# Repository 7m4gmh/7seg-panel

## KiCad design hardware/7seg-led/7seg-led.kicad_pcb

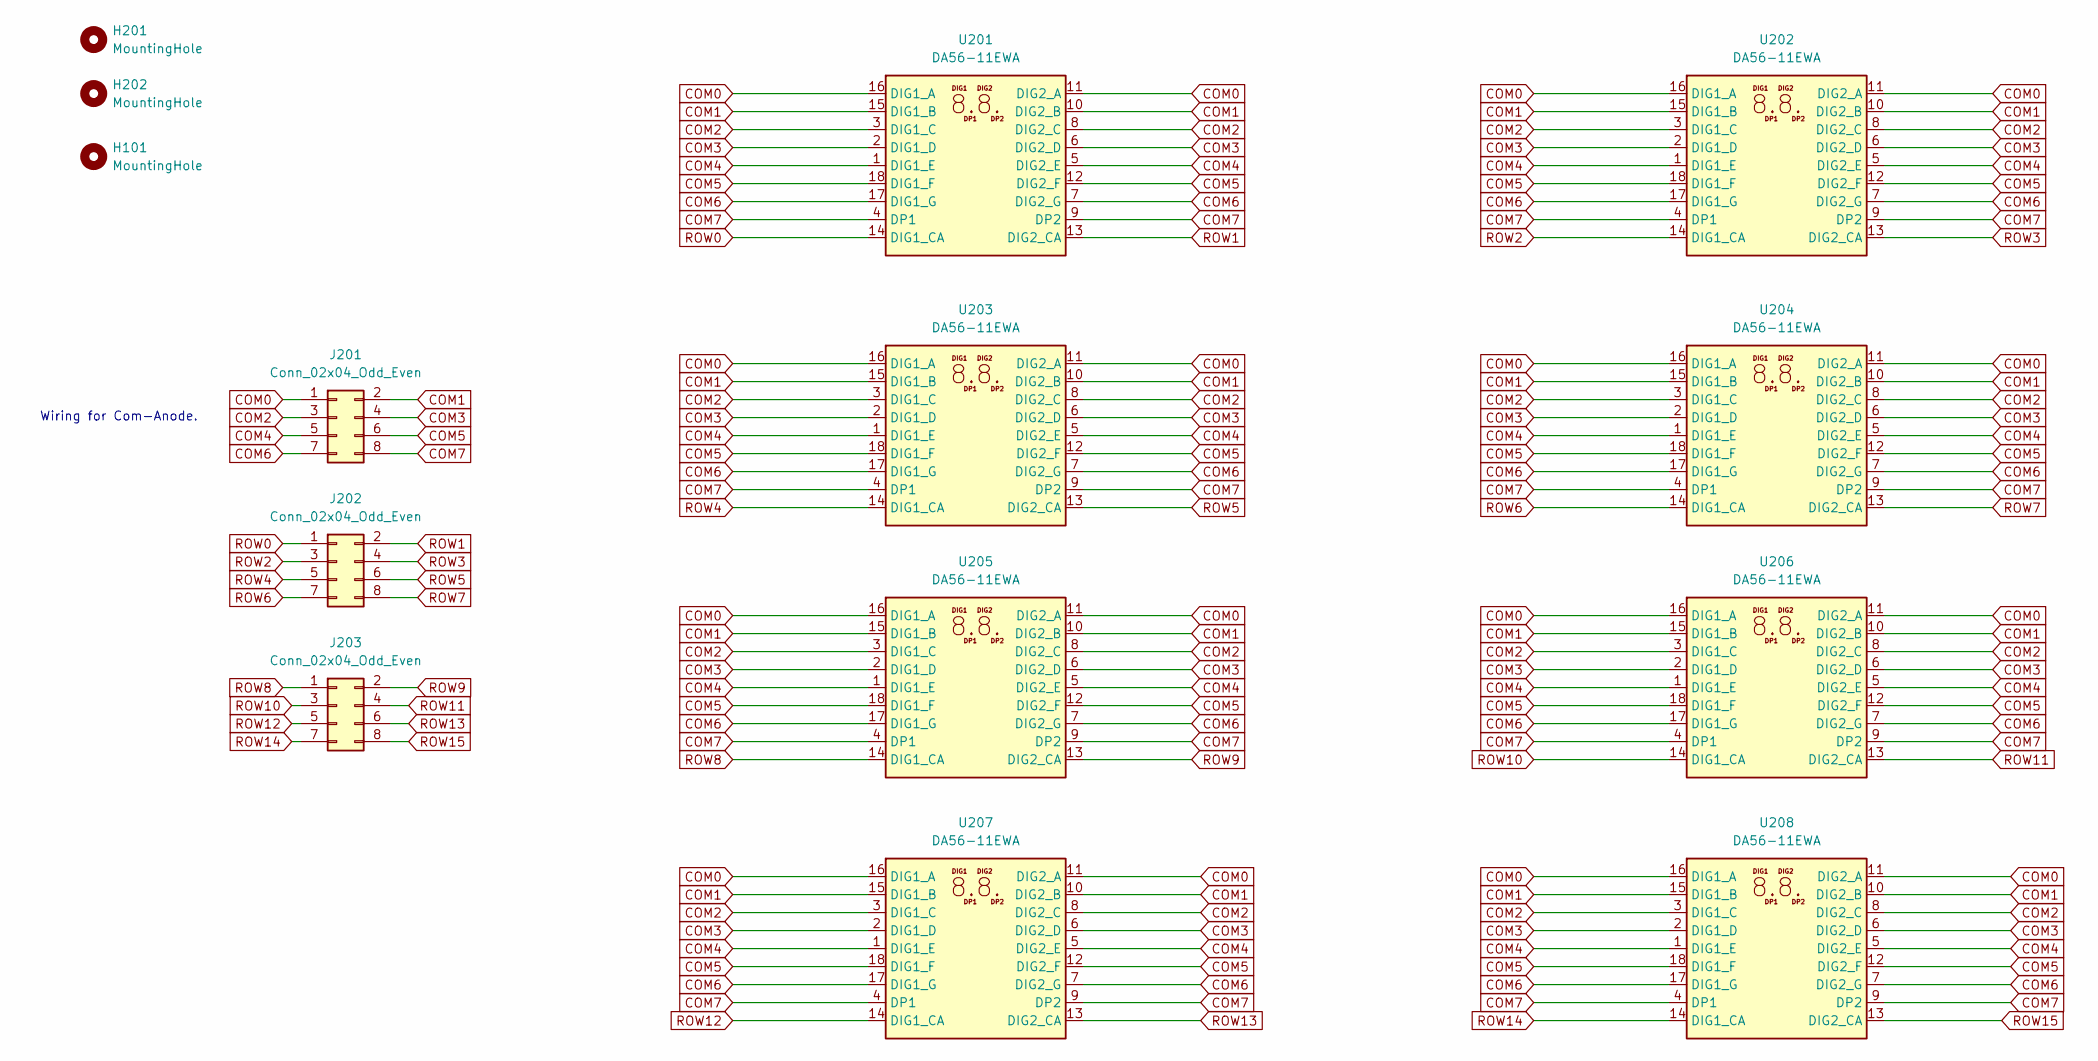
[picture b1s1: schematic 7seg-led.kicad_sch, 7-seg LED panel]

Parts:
H101, H201, H202: MountingHole; MountingHole_3.2mm_M3
J201, J202, J203: Conn_02x04_Odd_Even; PinHeader_2x04_P2.54mm_Vertical
U201, U202, U203, U204, U205, U206, U207, U208: DA56-11EWA; SL-9263

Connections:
COM0: J201.1, U201.11 (DIG2_A), U201.16 (DIG1_A), U202.11 (DIG2_A), U202.16 (DIG1_A), U203.11 (DIG2_A), U203.16 (DIG1_A), U204.11 (DIG2_A), U204.16 (DIG1_A), U205.11 (DIG2_A), U205.16 (DIG1_A), U206.11 (DIG2_A), U206.16 (DIG1_A), U207.11 (DIG2_A), U207.16 (DIG1_A), U208.11 (DIG2_A), U208.16 (DIG1_A)
COM1: J201.2, U201.10 (DIG2_B), U201.15 (DIG1_B), U202.10 (DIG2_B), U202.15 (DIG1_B), U203.10 (DIG2_B), U203.15 (DIG1_B), U204.10 (DIG2_B), U204.15 (DIG1_B), U205.10 (DIG2_B), U205.15 (DIG1_B), U206.10 (DIG2_B), U206.15 (DIG1_B), U207.10 (DIG2_B), U207.15 (DIG1_B), U208.10 (DIG2_B), U208.15 (DIG1_B)
COM2: J201.3, U201.3 (DIG1_C), U201.8 (DIG2_C), U202.3 (DIG1_C), U202.8 (DIG2_C), U203.3 (DIG1_C), U203.8 (DIG2_C), U204.3 (DIG1_C), U204.8 (DIG2_C), U205.3 (DIG1_C), U205.8 (DIG2_C), U206.3 (DIG1_C), U206.8 (DIG2_C), U207.3 (DIG1_C), U207.8 (DIG2_C), U208.3 (DIG1_C), U208.8 (DIG2_C)
COM3: J201.4, U201.2 (DIG1_D), U201.6 (DIG2_D), U202.2 (DIG1_D), U202.6 (DIG2_D), U203.2 (DIG1_D), U203.6 (DIG2_D), U204.2 (DIG1_D), U204.6 (DIG2_D), U205.2 (DIG1_D), U205.6 (DIG2_D), U206.2 (DIG1_D), U206.6 (DIG2_D), U207.2 (DIG1_D), U207.6 (DIG2_D), U208.2 (DIG1_D), U208.6 (DIG2_D)
COM4: J201.5, U201.1 (DIG1_E), U201.5 (DIG2_E), U202.1 (DIG1_E), U202.5 (DIG2_E), U203.1 (DIG1_E), U203.5 (DIG2_E), U204.1 (DIG1_E), U204.5 (DIG2_E), U205.1 (DIG1_E), U205.5 (DIG2_E), U206.1 (DIG1_E), U206.5 (DIG2_E), U207.1 (DIG1_E), U207.5 (DIG2_E), U208.1 (DIG1_E), U208.5 (DIG2_E)
COM5: J201.6, U201.12 (DIG2_F), U201.18 (DIG1_F), U202.12 (DIG2_F), U202.18 (DIG1_F), U203.12 (DIG2_F), U203.18 (DIG1_F), U204.12 (DIG2_F), U204.18 (DIG1_F), U205.12 (DIG2_F), U205.18 (DIG1_F), U206.12 (DIG2_F), U206.18 (DIG1_F), U207.12 (DIG2_F), U207.18 (DIG1_F), U208.12 (DIG2_F), U208.18 (DIG1_F)
COM6: J201.7, U201.7 (DIG2_G), U201.17 (DIG1_G), U202.7 (DIG2_G), U202.17 (DIG1_G), U203.7 (DIG2_G), U203.17 (DIG1_G), U204.7 (DIG2_G), U204.17 (DIG1_G), U205.7 (DIG2_G), U205.17 (DIG1_G), U206.7 (DIG2_G), U206.17 (DIG1_G), U207.7 (DIG2_G), U207.17 (DIG1_G), U208.7 (DIG2_G), U208.17 (DIG1_G)
COM7: J201.8, U201.4 (DP1), U201.9 (DP2), U202.4 (DP1), U202.9 (DP2), U203.4 (DP1), U203.9 (DP2), U204.4 (DP1), U204.9 (DP2), U205.4 (DP1), U205.9 (DP2), U206.4 (DP1), U206.9 (DP2), U207.4 (DP1), U207.9 (DP2), U208.4 (DP1), U208.9 (DP2)
ROW0: J202.1, U201.14 (DIG1_CA)
ROW1: J202.2, U201.13 (DIG2_CA)
ROW2: J202.3, U202.14 (DIG1_CA)
ROW3: J202.4, U202.13 (DIG2_CA)
ROW4: J202.5, U203.14 (DIG1_CA)
ROW5: J202.6, U203.13 (DIG2_CA)
ROW6: J202.7, U204.14 (DIG1_CA)
ROW7: J202.8, U204.13 (DIG2_CA)
ROW8: J203.1, U205.14 (DIG1_CA)
ROW9: J203.2, U205.13 (DIG2_CA)
ROW10: J203.3, U206.14 (DIG1_CA)
ROW11: J203.4, U206.13 (DIG2_CA)
ROW12: J203.5, U207.14 (DIG1_CA)
ROW13: J203.6, U207.13 (DIG2_CA)
ROW14: J203.7, U208.14 (DIG1_CA)
ROW15: J203.8, U208.13 (DIG2_CA)

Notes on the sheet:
Wiring for Com-Anode.

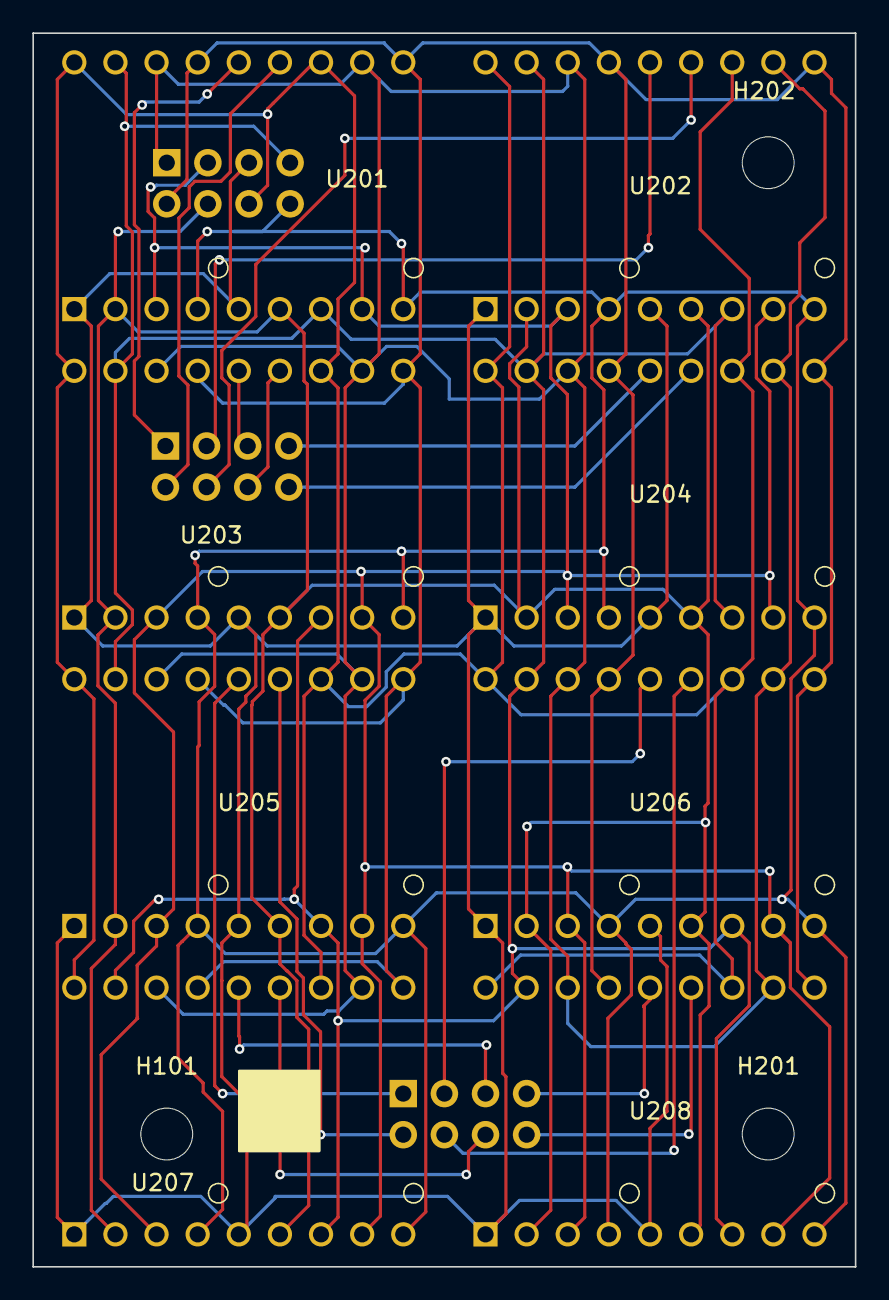
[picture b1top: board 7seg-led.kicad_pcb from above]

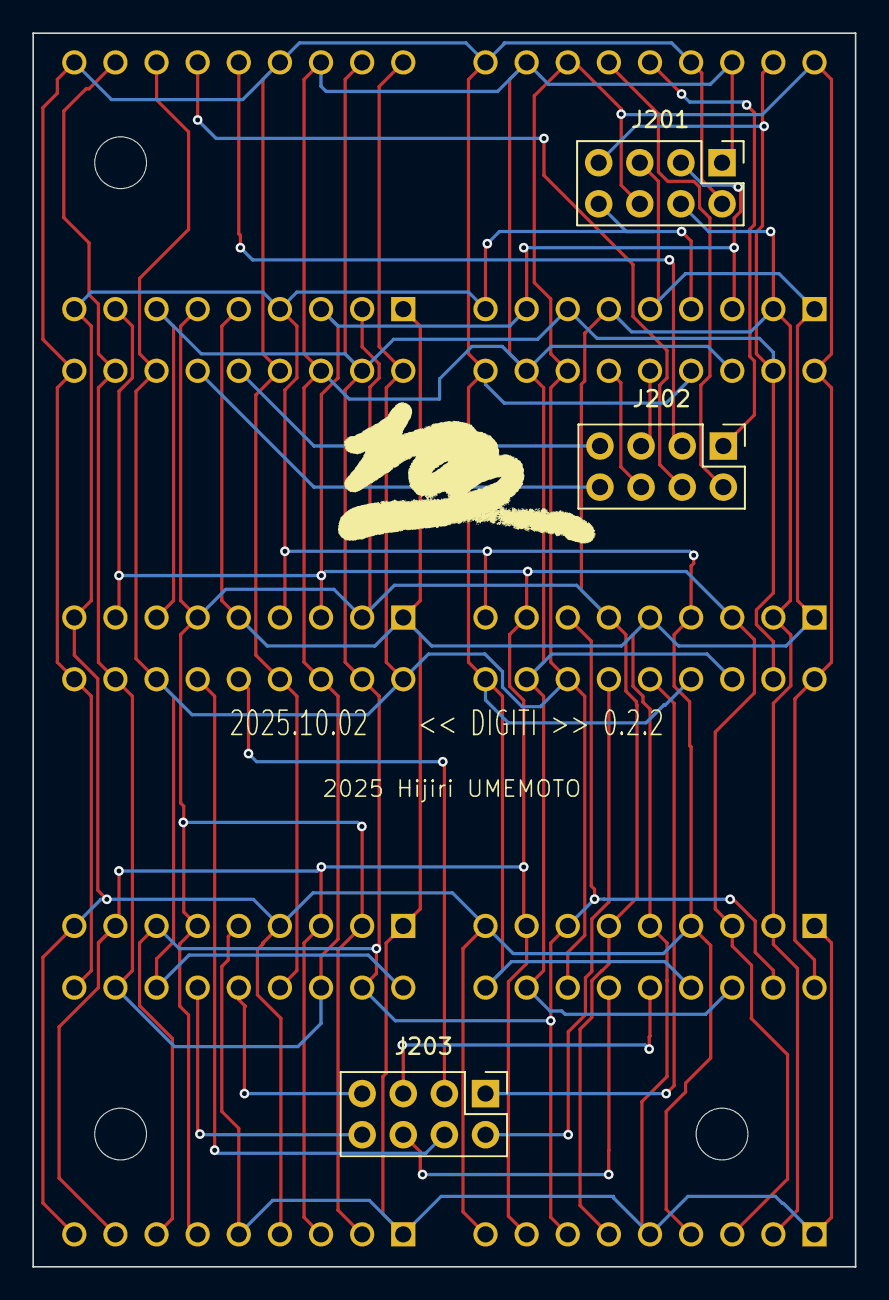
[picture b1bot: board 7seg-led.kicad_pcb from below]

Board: 2 copper layers, 50.8 x 76.2 mm, 14 parts (3 on the bottom side), 24 nets.

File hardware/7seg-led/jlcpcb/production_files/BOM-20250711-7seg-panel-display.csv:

Comment,Designator,Footprint,LCSC,Quantity
DA56-11EWA,U206,SL-9263,,1
DA56-11EWA,U202,SL-9263,,1
DA56-11EWA,U205,SL-9263,,1
DA56-11EWA,U201,SL-9263,,1
DA56-11EWA,U208,SL-9263,,1
DA56-11EWA,U204,SL-9263,,1
DA56-11EWA,U203,SL-9263,,1
DA56-11EWA,U207,SL-9263,,1
Conn_02x04_Odd_Even,J203,PinHeader_2x04_P2.54mm_Vertical,,1
Conn_02x04_Odd_Even,J202,PinHeader_2x04_P2.54mm_Vertical,,1
Conn_02x04_Odd_Even,J201,PinHeader_2x04_P2.54mm_Vertical,,1

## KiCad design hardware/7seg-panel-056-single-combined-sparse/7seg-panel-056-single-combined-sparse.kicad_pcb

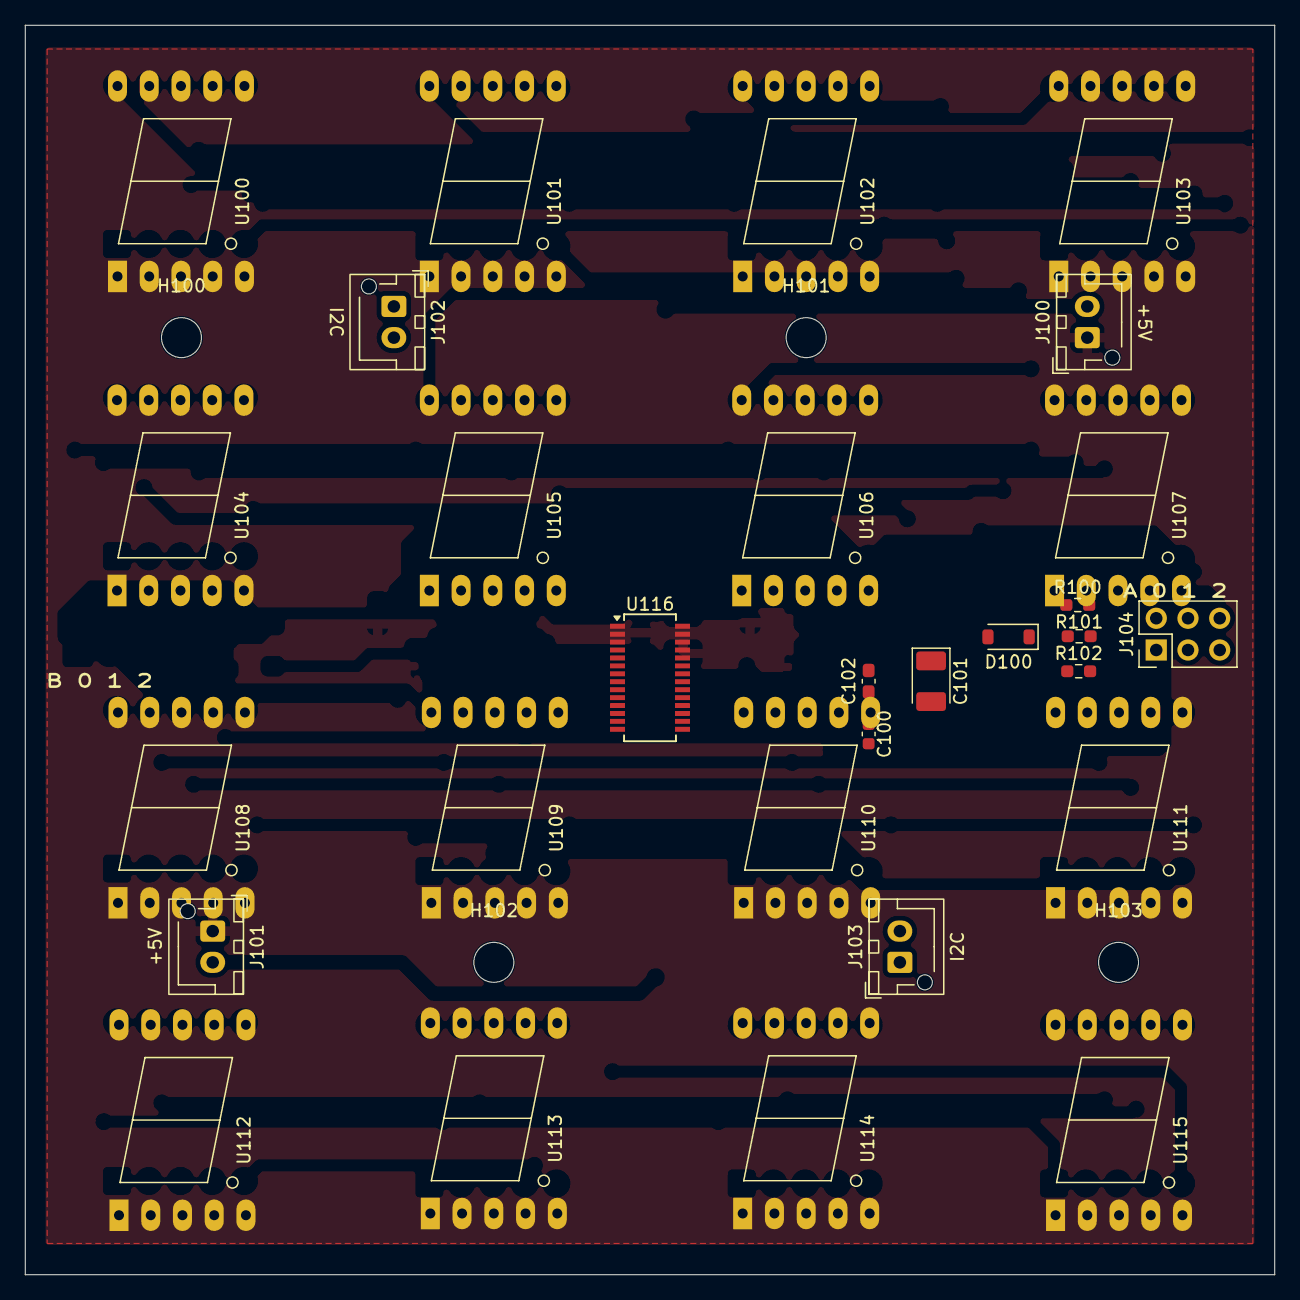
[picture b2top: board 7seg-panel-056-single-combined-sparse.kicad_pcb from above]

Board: 2 copper layers, 100.0 x 100.0 mm, 33 parts (0 on the bottom side), 32 nets, no tracks yet.

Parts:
C100: 22uF; C_0603_1608Metric
C101: 22uF; CP_EIA-3528-21_Kemet-B_HandSolder
C102: 0.1uF; C_0603_1608Metric_Pad1.08x0.95mm_HandSolder
D100: 1N4148W; D_SOD-123
H100, H101, H102, H103: MountingHole; MountingHole_3.2mm_M3
J100, J101: +5V; JST_XH_B2B-XH-AM_1x02_P2.50mm_Vertical
J102, J103: I2C; JST_XH_B2B-XH-AM_1x02_P2.50mm_Vertical
J104: Conn_02x03_Odd_Even; PinHeader_2x03_P2.54mm_Vertical
R100, R101, R102: 39kR; R_0603_1608Metric_Pad0.98x0.95mm_HandSolder
U100, U101, U102, U103, U104, U105, U106, U107, U108, U109, U110, U111, U112, U113, U114, U115: OSL10564-IRA; 7SegmentLED_OSL10564
U116: HT16K33-28-SSOPA; SSOP-28_3.9x9.9mm_P0.635mm

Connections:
A_COM0: D100.2 (A), U100.7 (A), U101.7 (A), U102.7 (A), U103.7 (A), U104.7 (A), U105.7 (A), U106.7 (A), U107.7 (A), U108.7 (A), U109.7 (A), U110.7 (A), U111.7 (A), U112.7 (A), U113.7 (A), U114.7 (A), U115.7 (A), U116.2 (COM0/AD)
A_COM1: U100.6 (B), U101.6 (B), U102.6 (B), U103.6 (B), U104.6 (B), U105.6 (B), U106.6 (B), U107.6 (B), U108.6 (B), U109.6 (B), U110.6 (B), U111.6 (B), U112.6 (B), U113.6 (B), U114.6 (B), U115.6 (B), U116.3 (COM1/KS0)
A_COM2: U100.4 (C), U101.4 (C), U102.4 (C), U103.4 (C), U104.4 (C), U105.4 (C), U106.4 (C), U107.4 (C), U108.4 (C), U109.4 (C), U110.4 (C), U111.4 (C), U112.4 (C), U113.4 (C), U114.4 (C), U115.4 (C), U116.4 (COM2/KS1)
A_COM3: U100.2 (D), U101.2 (D), U102.2 (D), U103.2 (D), U104.2 (D), U105.2 (D), U106.2 (D), U107.2 (D), U108.2 (D), U109.2 (D), U110.2 (D), U111.2 (D), U112.2 (D), U113.2 (D), U114.2 (D), U115.2 (D), U116.5 (COM3/KS2)
A_COM4: U100.1 (E), U101.1 (E), U102.1 (E), U103.1 (E), U104.1 (E), U105.1 (E), U106.1 (E), U107.1 (E), U108.1 (E), U109.1 (E), U110.1 (E), U111.1 (E), U112.1 (E), U113.1 (E), U114.1 (E), U115.1 (E), U116.6 (COM4)
A_COM5: U100.9 (F), U101.9 (F), U102.9 (F), U103.9 (F), U104.9 (F), U105.9 (F), U106.9 (F), U107.9 (F), U108.9 (F), U109.9 (F), U110.9 (F), U111.9 (F), U112.9 (F), U113.9 (F), U114.9 (F), U115.9 (F), U116.7 (COM5)
A_COM6: U100.10 (G), U101.10 (G), U102.10 (G), U103.10 (G), U104.10 (G), U105.10 (G), U106.10 (G), U107.10 (G), U108.10 (G), U109.10 (G), U110.10 (G), U111.10 (G), U112.10 (G), U113.10 (G), U114.10 (G), U115.10 (G), U116.8 (COM6)
A_COM7: U100.5 (DP), U101.5 (DP), U102.5 (DP), U103.5 (DP), U104.5 (DP), U105.5 (DP), U106.5 (DP), U107.5 (DP), U108.5 (DP), U109.5 (DP), U110.5 (DP), U111.5 (DP), U112.5 (DP), U113.5 (DP), U114.5 (DP), U115.5 (DP)
A_ROW0: J104.1, U100.3 (CA), U116.25 (ROW0/A2)
A_ROW1: J104.3, U101.3 (CA), U116.24 (ROW1/A1)
A_ROW2: J104.5, U102.3 (CA), U116.23 (ROW2/A0)
A_ROW3: U103.3 (CA), U116.22 (ROW3/K1)
A_ROW4: U104.3 (CA), U116.21 (ROW4/K2)
A_ROW5: U105.3 (CA), U116.20 (ROW5/K3)
A_ROW6: U106.3 (CA), U116.19 (ROW6/K4)
A_ROW7: U107.3 (CA), U116.18 (ROW7/K5)
A_ROW8: U108.3 (CA), U116.17 (ROW9/K6)
A_ROW9: U109.3 (CA), U116.16 (ROW9/K7)
A_ROW10: U110.3 (CA), U116.15 (ROW10/K8)
A_ROW11: U111.3 (CA), U116.14 (ROW11/K9)
A_ROW12: U112.3 (CA), U116.12 (ROW13/K12)
A_ROW13: U113.3 (CA), U116.13 (ROW12/K10)
A_ROW14: U114.3 (CA), U116.10 (ROW15/K13/INT)
A_ROW15: U115.3 (CA), U116.11 (ROW14/K12)
GND: C100.2, C101.2, C102.2, J100.1, J101.1, U116.1 (VCC)
unnamed: D100.1 (K), R100.1, R101.1, R102.1
unnamed: J104.2, R102.2
unnamed: J104.4, R101.2
unnamed: J104.6, R100.2
SCL: J102.2, J103.2, U116.26 (SCL)
SDA: J102.1, J103.1, U116.27 (SDA)
VDD: C100.1, C101.1, C102.1, J100.2, J101.2, U116.28 (VDD)

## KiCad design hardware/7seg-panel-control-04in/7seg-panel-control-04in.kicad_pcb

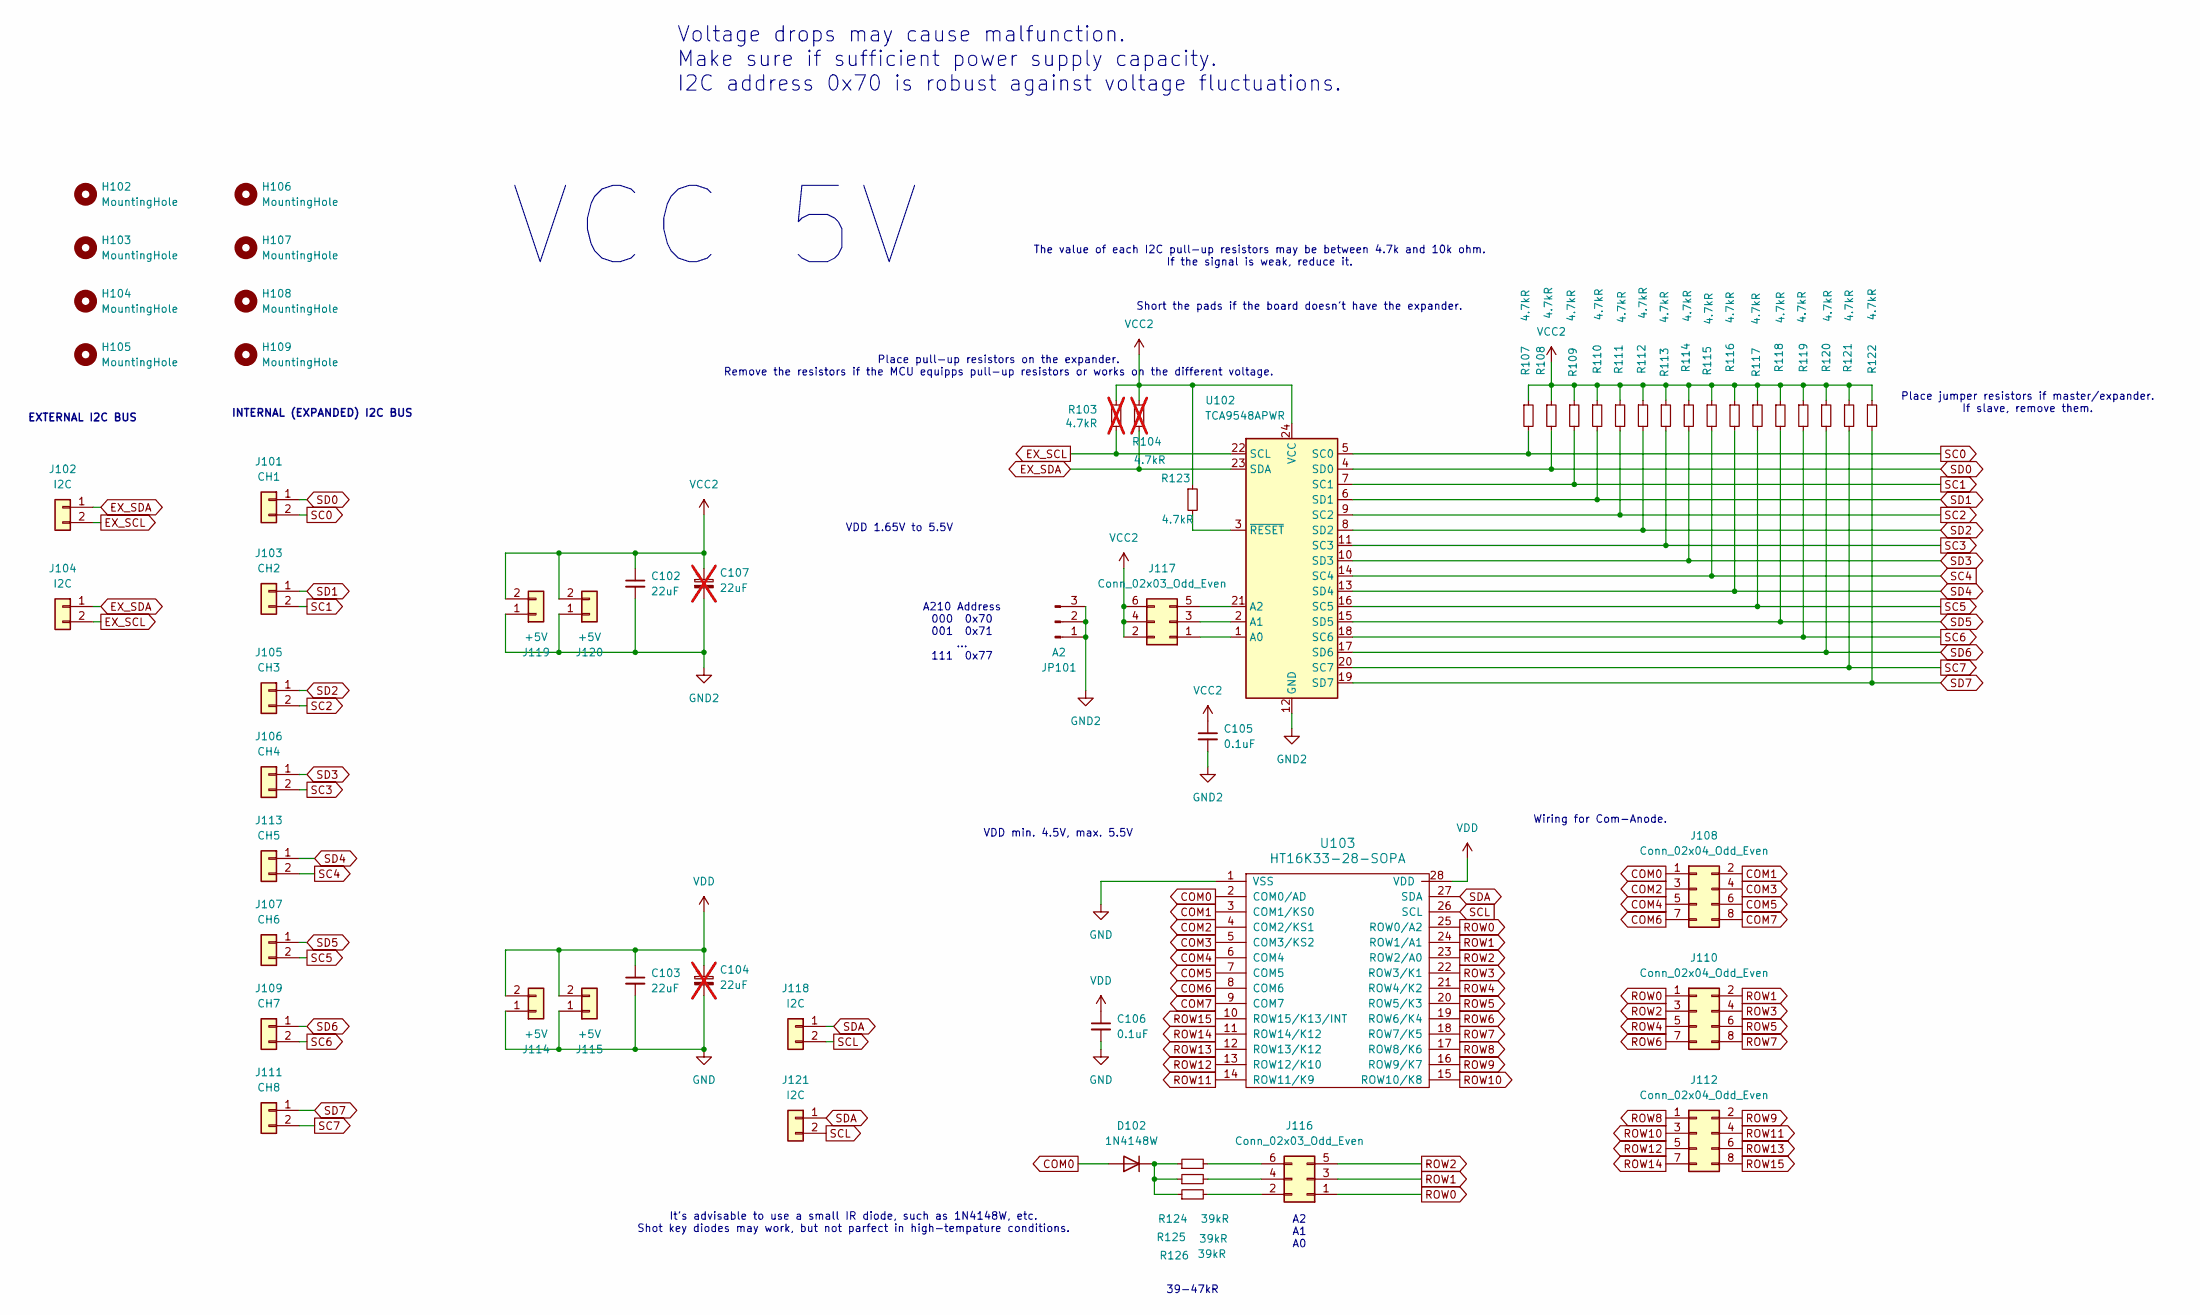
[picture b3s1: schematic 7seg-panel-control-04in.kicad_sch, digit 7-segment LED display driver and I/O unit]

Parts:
C102, C103: 22uF; C_0603_1608Metric
C104, C107: 22uF; CP_EIA-3528-21_Kemet-B_HandSolder; not fitted
C105, C106: 0.1uF; C_0603_1608Metric_Pad1.08x0.95mm_HandSolder
D102: 1N4148W; D_SOD-123
H102, H103, H104, H105, H106, H107, H108, H109: MountingHole; MountingHole_3.2mm_M3
J101: CH1; Generic_XH_S2B-XH-A-1_1x02_P2.50mm_Horizontal
J102, J104, J118, J121: I2C; JST_XH_B2B-XH-AM_1x02_P2.50mm_Vertical
J103: CH2; Generic_XH_S2B-XH-A-1_1x02_P2.50mm_Horizontal
J105: CH3; Generic_XH_S2B-XH-A-1_1x02_P2.50mm_Horizontal
J106: CH4; Generic_XH_S2B-XH-A-1_1x02_P2.50mm_Horizontal
J107: CH6; Generic_XH_S2B-XH-A-1_1x02_P2.50mm_Horizontal
J108, J110, J112: Conn_02x04_Odd_Even; PinSocket_2x04_P2.54mm_Vertical
J109: CH7; Generic_XH_S2B-XH-A-1_1x02_P2.50mm_Horizontal
J111: CH8; Generic_XH_S2B-XH-A-1_1x02_P2.50mm_Horizontal
J113: CH5; Generic_XH_S2B-XH-A-1_1x02_P2.50mm_Horizontal
J114, J115, J119, J120: +5V; JST_XH_B2B-XH-AM_1x02_P2.50mm_Vertical
J116, J117: Conn_02x03_Odd_Even; PinHeader_2x03_P2.54mm_Vertical
JP101: A2; PinHeader_1x03_P2.54mm_Vertical
R103, R104: 4.7kR; R_0603_1608Metric_Pad0.98x0.95mm_HandSolder; not fitted
R107, R108, R109, R110, R111, R112, R113, R114, R115, R116, R117, R118, R119, R120, R121, R122, R123: 4.7kR; R_0603_1608Metric_Pad0.98x0.95mm_HandSolder
R124, R125, R126: 39kR; R_0603_1608Metric_Pad0.98x0.95mm_HandSolder
U102: TCA9548APWR; TSSOP-24_4.4x7.8mm_P0.65mm
U103: HT16K33-28-SOPA; SOP-28_8.4x18.16mm_P1.27mm

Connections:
COM0: D102.2 (A), J108.1, U103.2 (COM0/AD)
COM1: J108.2, U103.3 (COM1/KS0)
COM2: J108.3, U103.4 (COM2/KS1)
COM3: J108.4, U103.5 (COM3/KS2)
COM4: J108.5, U103.6 (COM4)
COM5: J108.6, U103.7 (COM5)
COM6: J108.7, U103.8 (COM6)
COM7: J108.8, U103.9 (COM7)
EX_SCL: J102.2, J104.2, R103.2, U102.22 (SCL)
EX_SDA: J102.1, J104.1, R104.2, U102.23 (SDA)
GND: C103.2, C104.2, C106.2, J114.1, J115.1, U103.1 (VSS)
GND2: C102.2, C105.2, C107.2, J119.1, J120.1, JP101.1, JP101.2, JP101.3, U102.12 (GND)
unnamed: D102.1 (K), R124.1, R125.1, R126.1
unnamed: J116.2, R126.2
unnamed: J116.4, R125.2
unnamed: J116.6, R124.2
unnamed: J117.1, U102.1 (A0)
unnamed: J117.3, U102.2 (A1)
unnamed: J117.5, U102.21 (A2)
unnamed: R123.2, U102.3 (~RESET)
ROW0: J110.1, J116.1, U103.25 (ROW0/A2)
ROW1: J110.2, J116.3, U103.24 (ROW1/A1)
ROW2: J110.3, J116.5, U103.23 (ROW2/A0)
ROW3: J110.4, U103.22 (ROW3/K1)
ROW4: J110.5, U103.21 (ROW4/K2)
ROW5: J110.6, U103.20 (ROW5/K3)
ROW6: J110.7, U103.19 (ROW6/K4)
ROW7: J110.8, U103.18 (ROW7/K5)
ROW8: J112.1, U103.17 (ROW8/K6)
ROW9: J112.2, U103.16 (ROW9/K7)
ROW10: J112.3, U103.15 (ROW10/K8)
ROW11: J112.4, U103.14 (ROW11/K9)
ROW12: J112.5, U103.13 (ROW12/K10)
ROW13: J112.6, U103.12 (ROW13/K12)
ROW14: J112.7, U103.11 (ROW14/K12)
ROW15: J112.8, U103.10 (ROW15/K13/INT)
SC0: J101.2, R107.2, U102.5 (SC0)
SC1: J103.2, R109.2, U102.7 (SC1)
SC2: J105.2, R111.2, U102.9 (SC2)
SC3: J106.2, R113.2, U102.11 (SC3)
SC4: J113.2, R115.2, U102.14 (SC4)
SC5: J107.2, R117.2, U102.16 (SC5)
SC6: J109.2, R119.2, U102.18 (SC6)
SC7: J111.2, R121.2, U102.20 (SC7)
SCL: J118.2, J121.2, U103.26 (SCL)
SD0: J101.1, R108.2, U102.4 (SD0)
SD1: J103.1, R110.2, U102.6 (SD1)
SD2: J105.1, R112.2, U102.8 (SD2)
SD3: J106.1, R114.2, U102.10 (SD3)
SD4: J113.1, R116.2, U102.13 (SD4)
SD5: J107.1, R118.2, U102.15 (SD5)
SD6: J109.1, R120.2, U102.17 (SD6)
SD7: J111.1, R122.2, U102.19 (SD7)
SDA: J118.1, J121.1, U103.27 (SDA)
VCC2: C102.1, C105.1, C107.1, J117.2, J117.4, J117.6, J119.2, J120.2, R103.1, R104.1, R107.1, R108.1, R109.1, R110.1, R111.1, R112.1, R113.1, R114.1, R115.1, R116.1, R117.1, R118.1, R119.1, R120.1, R121.1, R122.1, R123.1, U102.24 (VCC)
VDD: C103.1, C104.1, C106.1, J114.2, J115.2, U103.28 (VDD)

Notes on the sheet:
A210 Address 000 0x70 001 0x71 ... 111 0x77
Place jumper resistors if master/expander. If slave, remove them.
Voltage drops may cause malfunction. Make sure if sufficient power supply capacity. I2C address 0x70 is robust against voltage fluctuations.
39-47kR
It's advisable to use a small IR diode, such as 1N4148W, etc. Shot key diodes may work, but not parfect in high-tempature conditions.
Wiring for Com-Anode.
A2 A1 A0
VCC 5V
Place pull-up resistors on the expander. Remove the resistors if the MCU equipps pull-up resistors or works on the different voltage.
Short the pads if the board doesn't have the expander.
EXTERNAL I2C BUS
The value of each I2C pull-up resistors may be between 4.7k and 10k ohm. If the signal is weak, reduce it.
VDD 1.65V to 5.5V
INTERNAL (EXPANDED) I2C BUS
VDD min. 4.5V, max. 5.5V

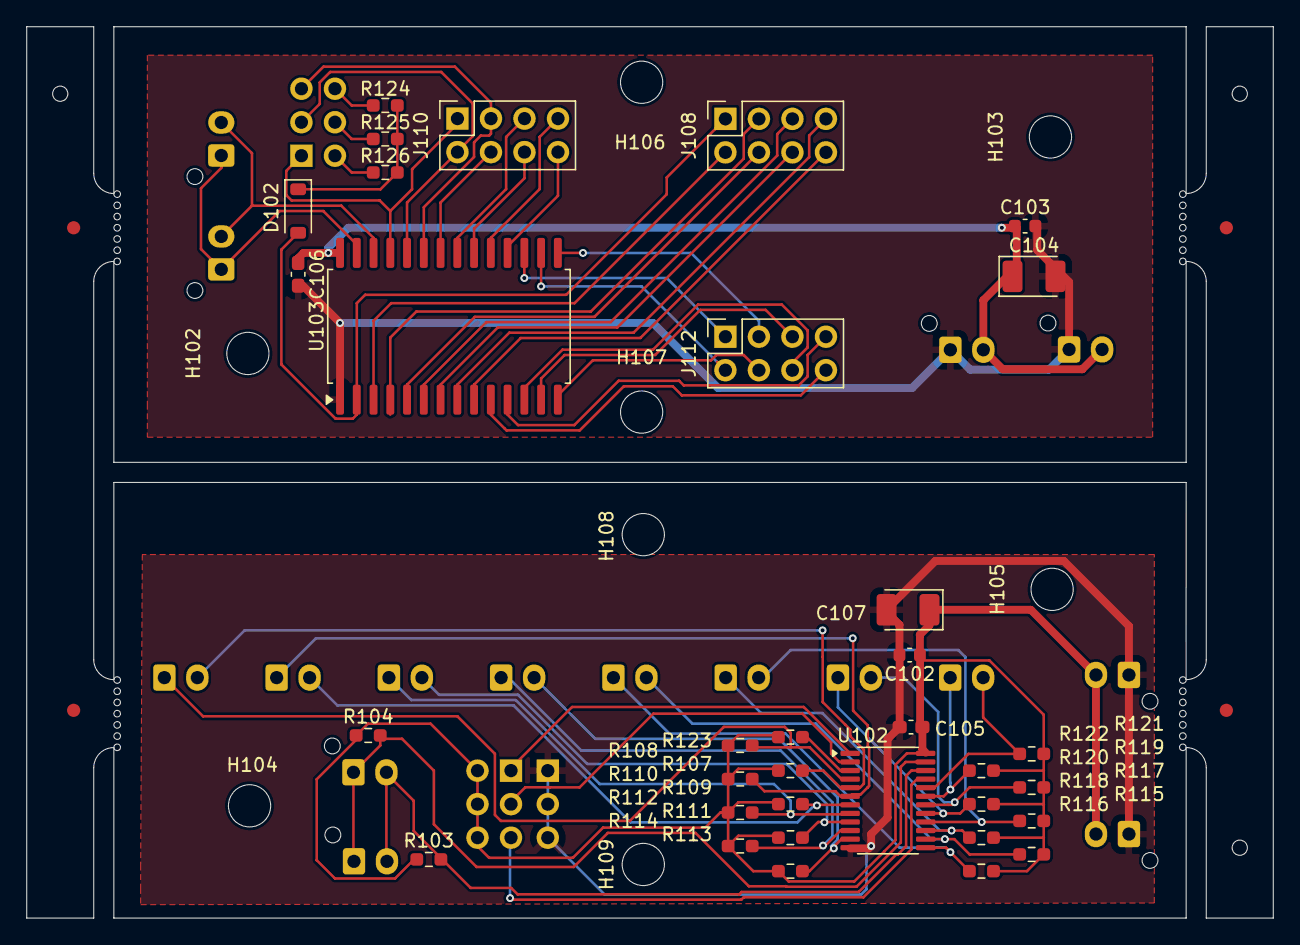
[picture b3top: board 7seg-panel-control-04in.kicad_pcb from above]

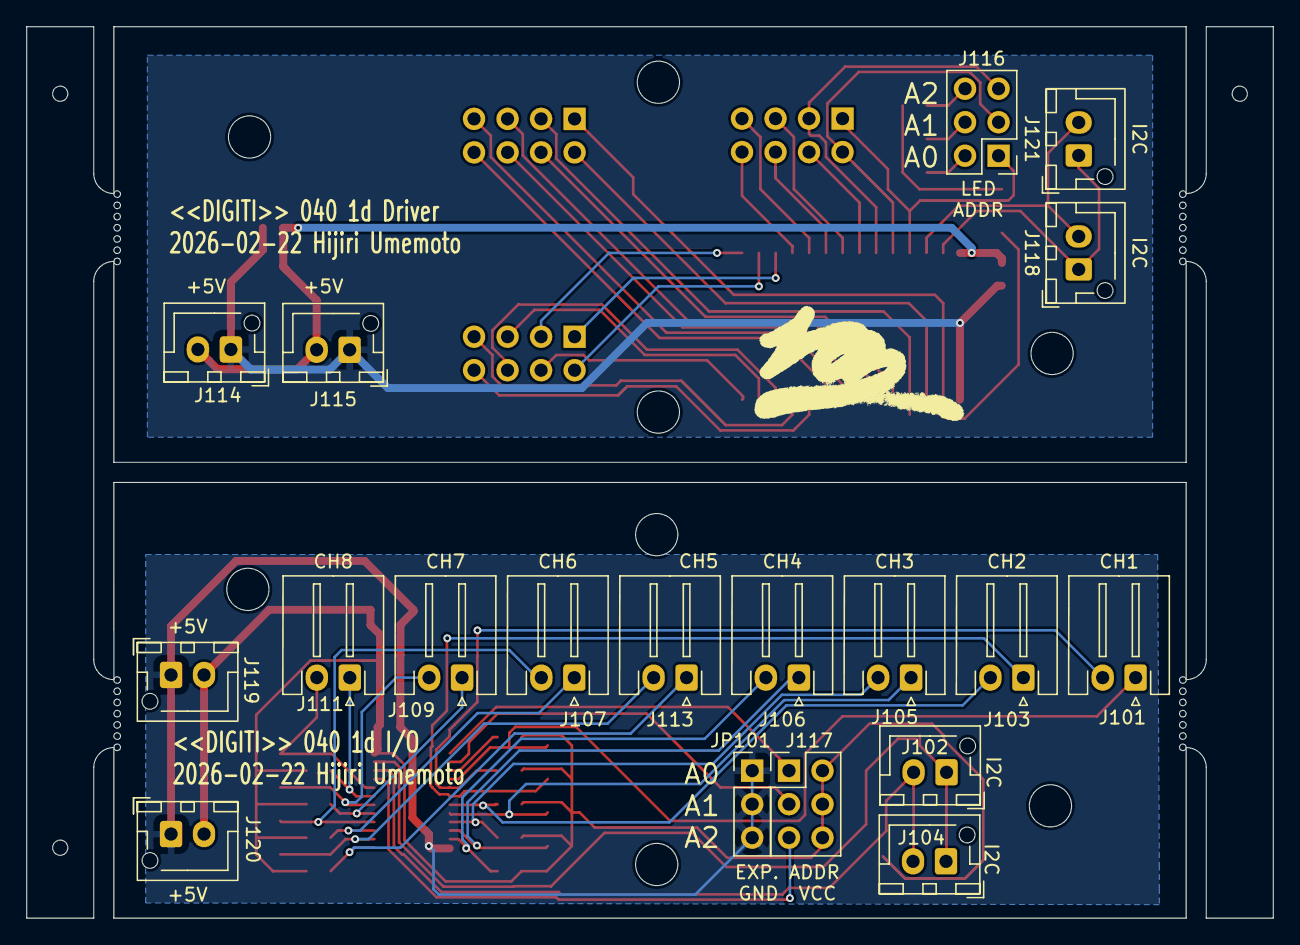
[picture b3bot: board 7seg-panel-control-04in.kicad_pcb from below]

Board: 2 copper layers, 94.5 x 67.6 mm, 61 parts (19 on the bottom side), 56 nets.
